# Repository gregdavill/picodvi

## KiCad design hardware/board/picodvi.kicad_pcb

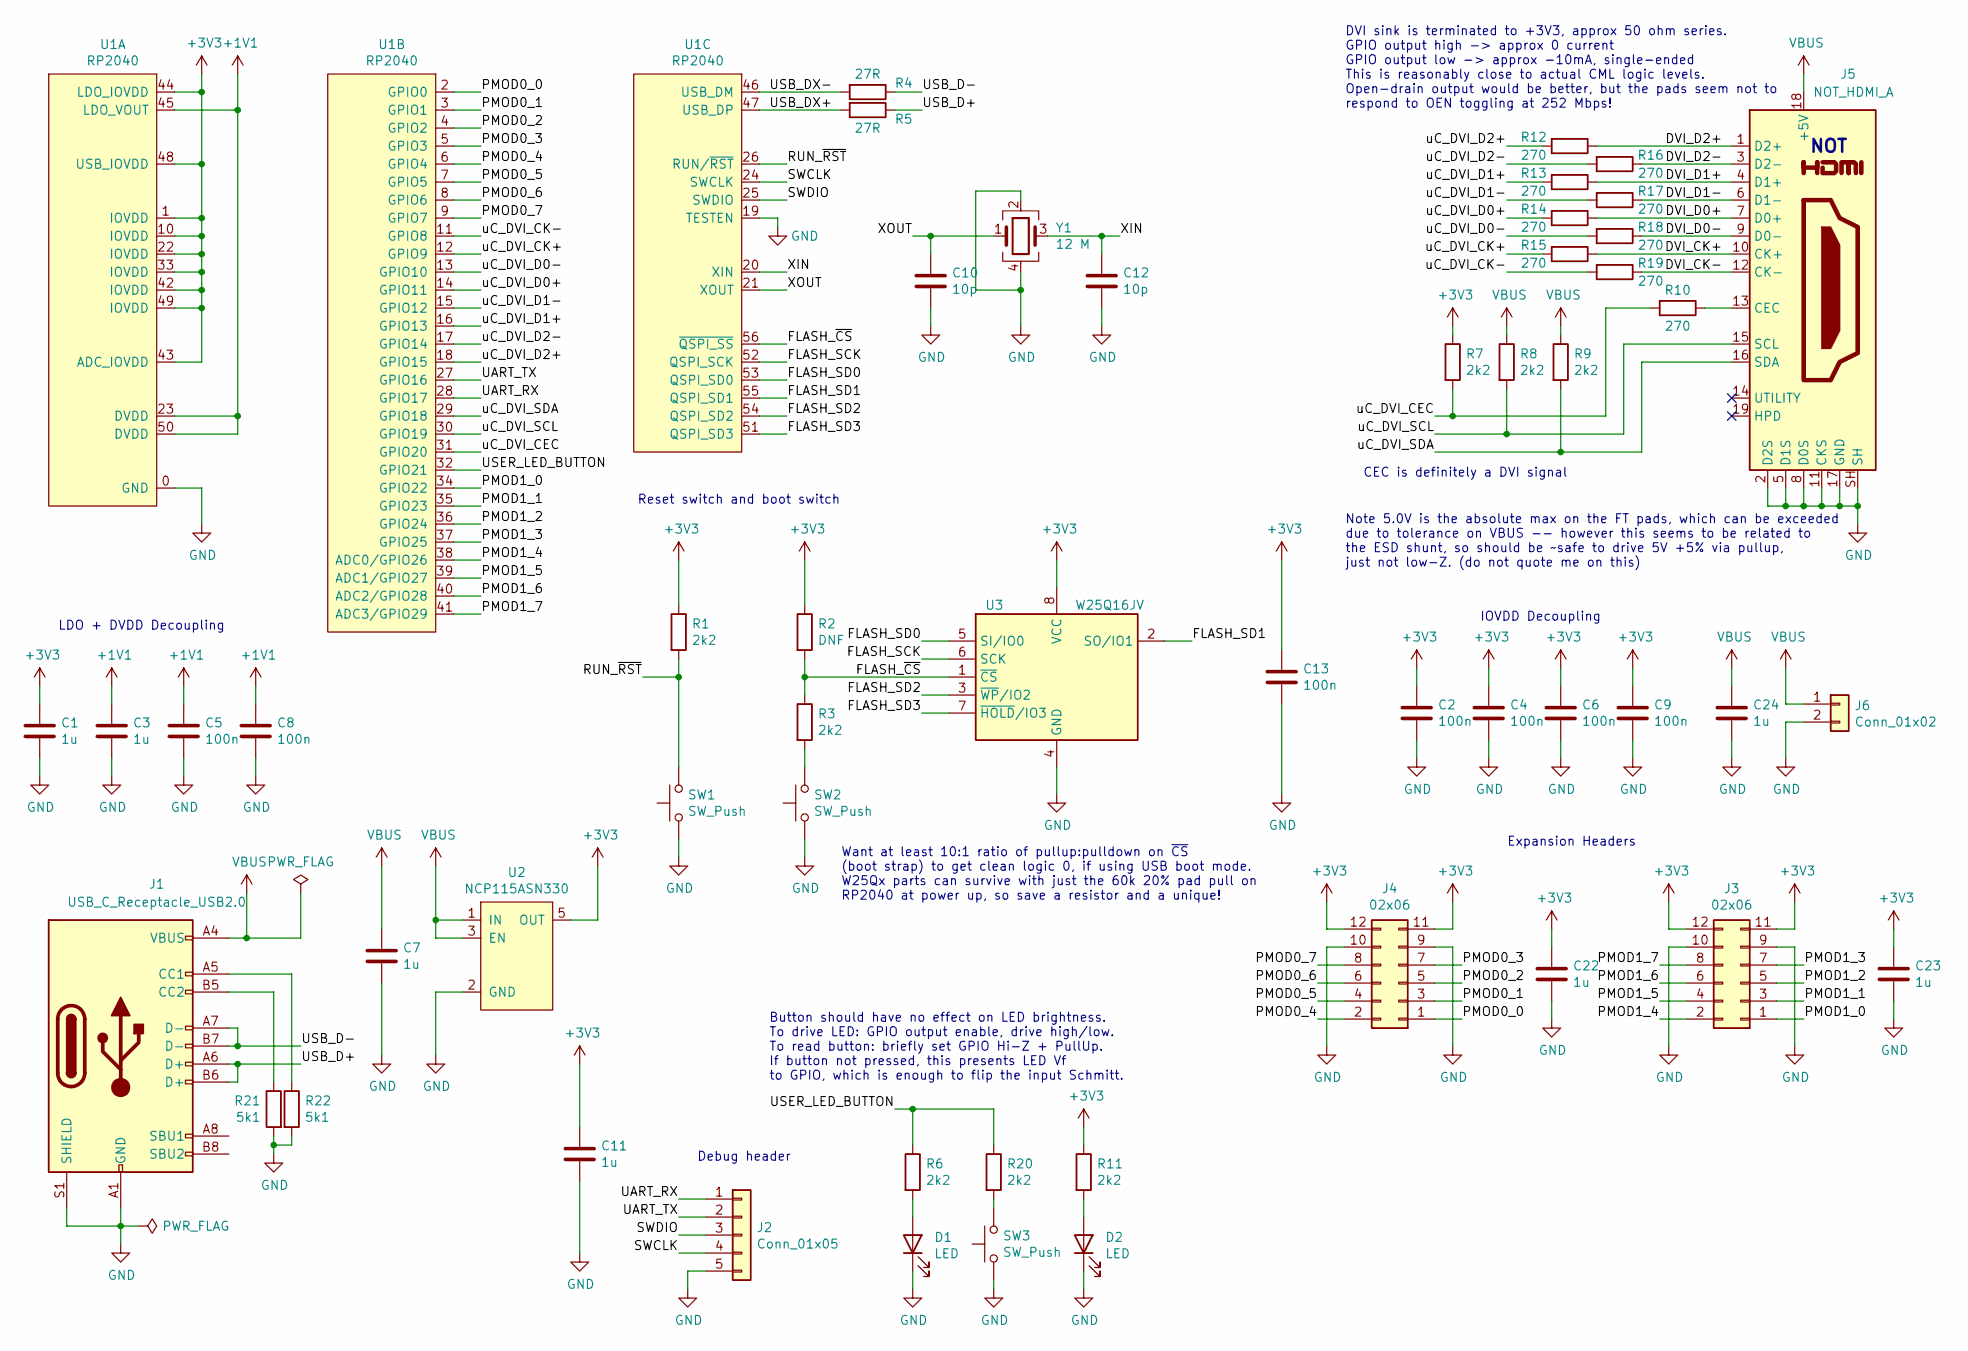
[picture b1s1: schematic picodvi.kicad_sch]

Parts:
C1, C3, C7, C11, C22, C23, C24: 1u; C_0402_1005Metric
C2, C4, C5, C6, C8, C9, C13: 100n; C_0402_1005Metric
C10, C12: 10p; C_0402_1005Metric
D1, D2: LED; LED_0805_2012Metric
J1: USB_C_Receptacle_USB2.0; USB_C_Receptacle_XKB_U262-16XN-4BVC11
J2: Conn_01x05; PinHeader_1x05_P2.54mm_Vertical
J3, J4: 02x06; PinHeader_2x06_P2.54mm_Horizontal
J5: NOT_HDMI_A; HDMI-SS-53000
J6: Conn_01x02; PinHeader_1x02_P2.54mm_Vertical
R1, R3, R6, R7, R8, R9, R11, R20: 2k2; R_0402_1005Metric
R2: DNF; R_0402_1005Metric
R4, R5: 27R; R_0402_1005Metric
R10, R12, R13, R14, R15, R16, R17, R18, R19: 270; R_0201_0603Metric
R21, R22: 5k1; R_0402_1005Metric
SW1, SW2, SW3: SW_Push; SW_SPST_PTS815
U1: RP2040; QFN-56_EP_7x7_Pitch0.4mm
U2: NCP115ASN330; SOT-23-5
U3: W25Q16JV; WSON-8-1EP_6x5mm_P1.27mm_EP3.4x4mm
Y1: 12 M; Crystal_SMD_3225-4Pin_3.2x2.5mm

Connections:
+1V1: C3.1, C5.1, C8.1, U1.23 (DVDD), U1.45 (LDO_VOUT), U1.50 (DVDD)
+3V3: C1.1, C2.1, C4.1, C6.1, C9.1, C11.1, C13.1, C22.1, C23.1, J3.11, J3.12, J4.11, J4.12, R1.1, R2.1, R7.1, R11.1, U1.1 (IOVDD), U1.10 (IOVDD), U1.22 (IOVDD), U1.33 (IOVDD), U1.42 (IOVDD), U1.43 (ADC_IOVDD), U1.44 (LDO_IOVDD), U1.48 (USB_IOVDD), U1.49 (IOVDD), U2.5 (OUT), U3.8 (VCC)
/DVI_CK+: J5.10 (CK+), R15.1
/DVI_CK-: J5.12 (CK-), R19.1
/DVI_D0+: J5.7 (D0+), R14.1
/DVI_D0-: J5.9 (D0-), R18.1
/DVI_D1+: J5.4 (D1+), R13.1
/DVI_D1-: J5.6 (D1-), R17.1
/DVI_D2+: J5.1 (D2+), R12.1
/DVI_D2-: J5.3 (D2-), R16.1
/FLASH_SCK: U1.52 (QSPI_SCK), U3.6 (SCK)
/FLASH_SD0: U1.53 (QSPI_SD0), U3.5 (SI/IO0)
/FLASH_SD1: U1.55 (QSPI_SD1), U3.2 (SO/IO1)
/FLASH_SD2: U1.54 (QSPI_SD2), U3.3 (~WP~/IO2)
/FLASH_SD3: U1.51 (QSPI_SD3), U3.7 (~HOLD~/IO3)
/FLASH_~CS~: R2.2, R3.1, U1.56 (~QSPI_SS~), U3.1 (~CS)
/PMOD0_0: J4.1, U1.2 (GPIO0)
/PMOD0_1: J4.3, U1.3 (GPIO1)
/PMOD0_2: J4.5, U1.4 (GPIO2)
/PMOD0_3: J4.7, U1.5 (GPIO3)
/PMOD0_4: J4.2, U1.6 (GPIO4)
/PMOD0_5: J4.4, U1.7 (GPIO5)
/PMOD0_6: J4.6, U1.8 (GPIO6)
/PMOD0_7: J4.8, U1.9 (GPIO7)
/PMOD1_0: J3.1, U1.34 (GPIO22)
/PMOD1_1: J3.3, U1.35 (GPIO23)
/PMOD1_2: J3.5, U1.36 (GPIO24)
/PMOD1_3: J3.7, U1.37 (GPIO25)
/PMOD1_4: J3.2, U1.38 (ADC0/GPIO26)
/PMOD1_5: J3.4, U1.39 (ADC1/GPIO27)
/PMOD1_6: J3.6, U1.40 (ADC2/GPIO28)
/PMOD1_7: J3.8, U1.41 (ADC3/GPIO29)
/RUN_~RST~: R1.2, SW1.2, U1.26 (RUN/~RST~)
/SWCLK: J2.4, U1.24 (SWCLK)
/SWDIO: J2.3, U1.25 (SWDIO)
/UART_RX: J2.1, U1.28 (GPIO17)
/UART_TX: J2.2, U1.27 (GPIO16)
/USB_D+: J1.A6 (D+), J1.B6 (D+), R5.1
/USB_D-: J1.A7 (D-), J1.B7 (D-), R4.1
/USB_DX+: R5.2, U1.47 (USB_DP)
/USB_DX-: R4.2, U1.46 (USB_DM)
/USER_LED_BUTTON: R6.1, R20.1, U1.32 (GPIO21)
/XIN: C12.1, U1.20 (XIN), Y1.3
/XOUT: C10.1, U1.21 (XOUT), Y1.1
/uC_DVI_CEC: R7.2, R10.2, U1.31 (GPIO20)
/uC_DVI_CK+: R15.2, U1.12 (GPIO9)
/uC_DVI_CK-: R19.2, U1.11 (GPIO8)
/uC_DVI_D0+: R14.2, U1.14 (GPIO11)
/uC_DVI_D0-: R18.2, U1.13 (GPIO10)
/uC_DVI_D1+: R13.2, U1.16 (GPIO13)
/uC_DVI_D1-: R17.2, U1.15 (GPIO12)
/uC_DVI_D2+: R12.2, U1.18 (GPIO15)
/uC_DVI_D2-: R16.2, U1.17 (GPIO14)
/uC_DVI_SCL: J5.15 (SCL), R8.2, U1.30 (GPIO19)
/uC_DVI_SDA: J5.16 (SDA), R9.2, U1.29 (GPIO18)
GND: C1.2, C2.2, C3.2, C4.2, C5.2, C6.2, C7.2, C8.2, C9.2, C10.2, C11.2, C12.2, C13.2, C22.2, C23.2, C24.2, D1.1 (K), D2.1 (K), J1.A1 (GND), J1.A12 (GND), J1.B1 (GND), J1.B12 (GND), J1.S1 (SHIELD), J2.5, J3.9, J3.10, J4.9, J4.10, J5.2 (D2S), J5.5 (D1S), J5.8 (D0S), J5.11 (CKS), J5.17 (GND), J5.SH, J6.2, R21.2, R22.2, SW1.1, SW2.1, SW3.1, U1.0 (GND), U1.19 (TESTEN), U2.2 (GND), U3.4 (GND), Y1.2, Y1.4
unnamed: D1.2 (A), R6.2
unnamed: D2.2 (A), R11.2
unnamed: J1.A5 (CC1), R22.1
unnamed: J1.B5 (CC2), R21.1
unnamed: J5.13 (CEC), R10.1
unnamed: R3.2, SW2.2
unnamed: R20.2, SW3.2
VBUS: C7.1, C24.1, J1.A4 (VBUS), J1.A9 (VBUS), J1.B4 (VBUS), J1.B9 (VBUS), J5.18 (+5V), J6.1, R8.1, R9.1, U2.1 (IN), U2.3 (EN)
no_connect_67: J5.14 (UTILITY)
no_connect_68: J5.19 (HPD)

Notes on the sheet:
LDO + DVDD Decoupling
Debug header
Button should have no effect on LED brightness. To drive LED: GPIO output enable, drive high/low. To read button: briefly set GPIO Hi-Z + PullUp. If button not pressed, this presents LED Vf to GPIO, which is enough to flip the input Schmitt.
Reset switch and boot switch
Want at least 10:1 ratio of pullup:pulldown on ~CS~ (boot strap) to get clean logic 0, if using USB boot mode. W25Qx parts can survive with just the 60k 20% pad pull on RP2040 at power up, so save a resistor and a unique!
DVI sink is terminated to +3V3, approx 50 ohm series. GPIO output high -> approx 0 current GPIO output low -> approx -10mA, single-ended This is reasonably close to actual CML logic levels. Open-drain output would be better, but the pads seem not to respond to OEN toggling at 252 Mbps!
Note 5.0V is the absolute max on the FT pads, which can be exceeded due to tolerance on VBUS -- however this seems to be related to the ESD shunt, so should be ~~safe to drive 5V +5% via pullup, just not low-Z. (do not quote me on this)
CEC is definitely a DVI signal
IOVDD Decoupling
Expansion Headers
NOT

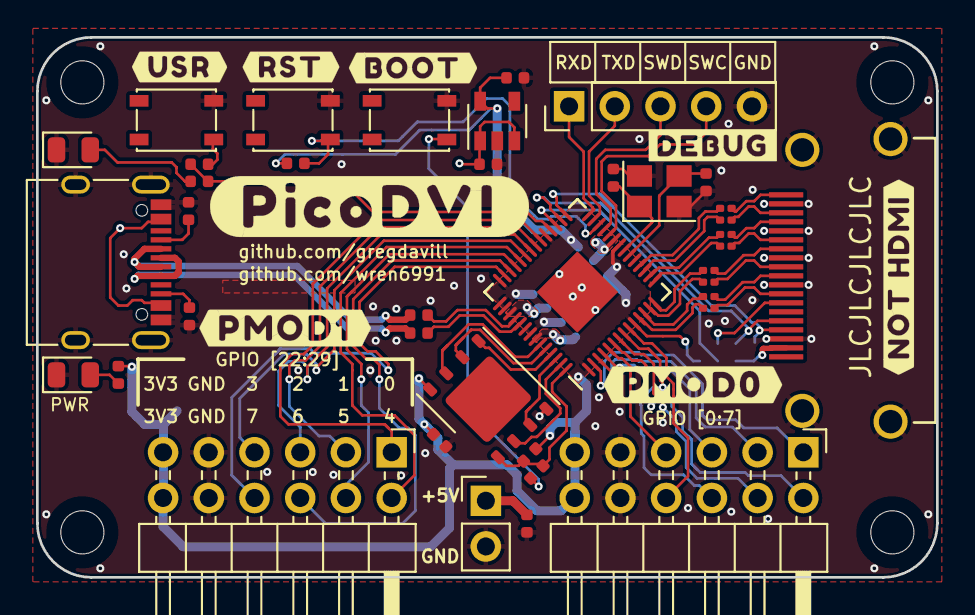
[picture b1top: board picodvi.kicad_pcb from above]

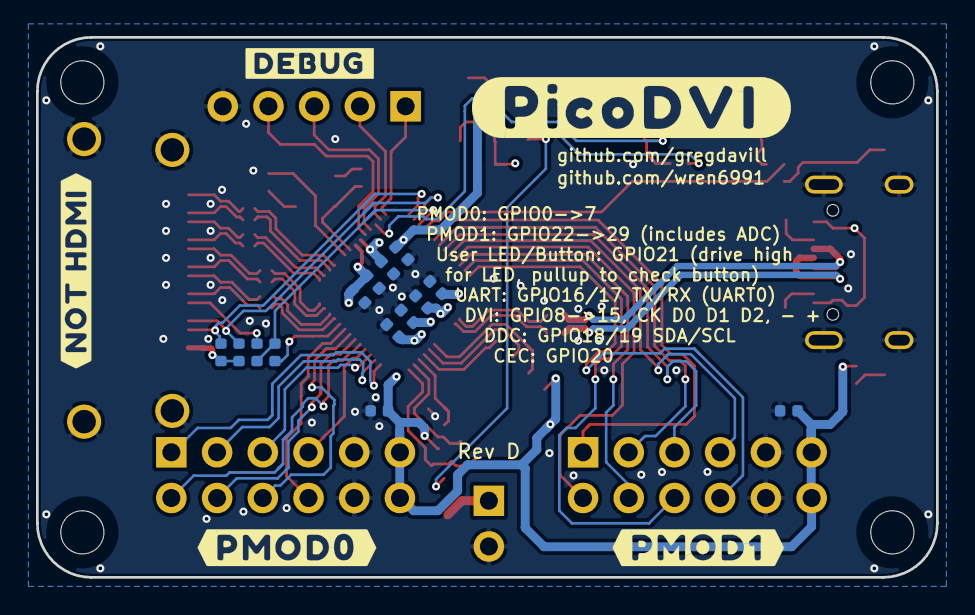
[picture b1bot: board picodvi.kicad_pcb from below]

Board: 4 copper layers, 50.0 x 30.0 mm, 53 parts (14 on the bottom side), 64 nets.

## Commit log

2021-01-22 Small updates to PCB
    - USB-C
    - Silkscreen lables
